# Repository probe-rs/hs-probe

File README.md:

# The Rusty High-speed Probe

This is an open hardware probe for the Serial Wire Debug (SWD) and JTAG protocol. It utilizes an
STM32F723 MCU which has an USB 2.0 High-speed Phy.

## Firmware

The firmware is available here and is open-source: https://github.com/probe-rs/hs-probe-firmware

## Features

There is an USB MUX on the board, so when the probe starts it enumerates in USB FS where one can
access the internal bootloader, and then when the firmware takes over it can switch to the USB HS.

* The output connector can either be:
    * The STDC14 connector used on STLink/V3 which is mounted by default.
    * Or the standard Cortex-M Debug (1.27mm, 10 pin) connector if one bends/removes the outer 2 pins on the connector.
* The programming connector is the Tag Connect TC2030, however for just loading firmware the USB bootloader is recommended.
* Resistive MUX between USB HS/FS.
* Castellated vias for all programming pins, power and 2 GPIOs.
* USB-C connector.
* Target 5V and `Vtarget` is protected with an ideal diode circuit to not have current flow from the target to the host.
* The probe support 1.8v - 3.3v signal voltage and `Vtarget`
* For compatibility (mainly with Tag-Connect TC2050), pin 7 on the STDC 14 can be connected to the protected 5V.

The schematic can be found in [the schematic PDF](schematic-v1.3.pdf).

## Cable Assembly

The hs-probe package sold on our [shop](https://shop.probe.rs) contains two 16 wire ribbon cables, three 14p connectors and one 10p connector.
You can make one cable with a 14p connector on each side and one cable with a 14p connector on one and a 10p connector on the other side. How to align the connectors is explained in the image below:

## License

This work is licensed under [CERN-OHL-P](cern_ohl_p_v2.txt).

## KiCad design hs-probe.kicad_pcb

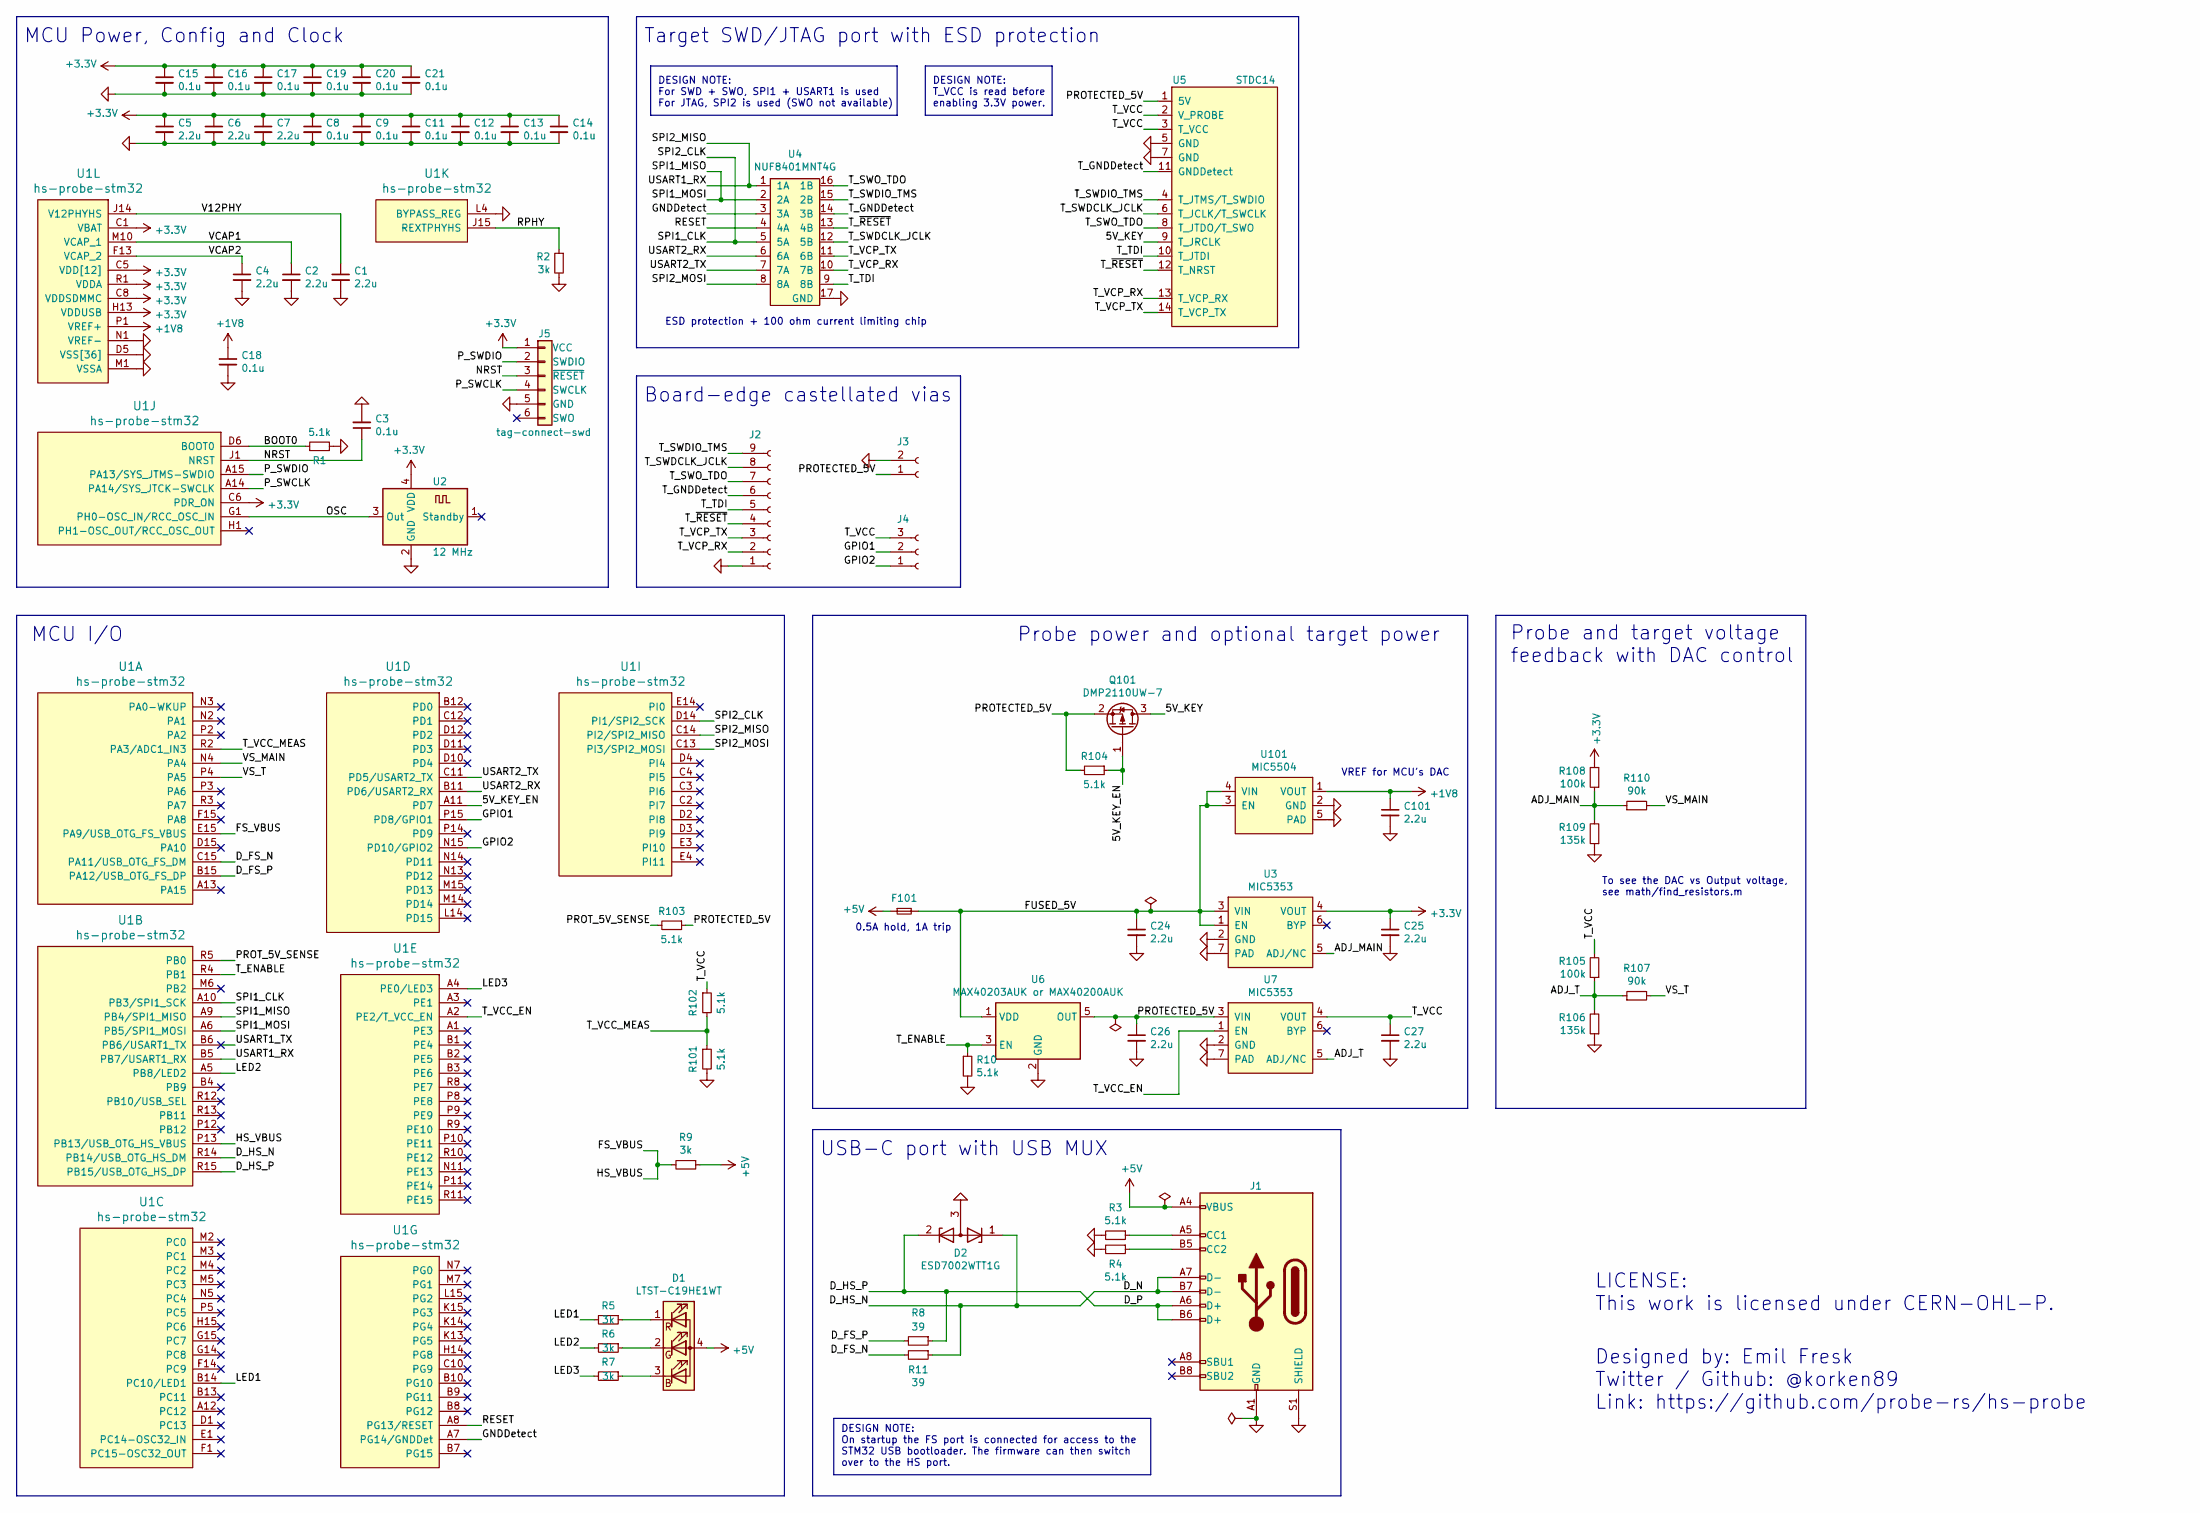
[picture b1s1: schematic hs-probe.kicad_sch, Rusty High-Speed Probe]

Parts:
C1, C2, C4, C5, C6, C7, C24, C25, C26, C27, C101: 2.2u; C_0402; Tolerance 10V, X5R
C3, C8, C9, C11, C12, C13, C14, C15, C16, C17, C18, C19, C20, C21: 0.1u; C_0402; Tolerance 25V, X7R
D1: LTST-C19HE1WT; LED_LiteOn_LTST-C19HE1WT; MPN LTST-C19HE1WT
D2: ESD7002WTT1G; SOT-323
F101: Fuse_Small; Fuse_0603_1608Metric
J1: USB_C_Receptacle_USB2.0; USB_C_Receptacle_USB4105; MPN C167321 (lcsc.com)
J2: Castellated Vias; 1x9_1.5mm_castellated
J3: Castellated Vias; 1x2_1.5mm_castellated
J4: Castellated Vias; 1x3_1.5mm_castellated
J5: tag-connect-swd; Tag-Connect_TC2030-IDC-NL_2x03_P1.27mm_Vertical
Q101: DMP2110UW-7; SOT-323
R1, R3, R4, R10, R101, R102, R103, R104: 5.1k; R_0402; Tolerance 1%
R2, R5, R6, R7, R9: 3k; R_0402; Tolerance 1%
R8, R11: 39; R_0402; Tolerance 1%
R105, R108: 100k; R_0402; Tolerance 1%
R106, R109: 135k; R_0402; Tolerance 1%
R107, R110: 90k; R_0402; Tolerance 1%
U1: hs-probe-stm32; UFBGA-201_10x10mm_Layout15x15_P0.65mm; MPN STM32F723IEK6
U2: 12 MHz; Crystal_4Pin_2.0x1.6mm; MPN KC2016Z12.0000C15XXK
U3, U7: MIC5353; DFN-6-1EP_1.6x1.6mm_P0.5mm_EP0.5x1.26mm
U4: NUF8401MNT4G; DFN-16-1EP_1.6x4mm_P0.5mm; MPN NUF8401MNT4G
U5: STDC14; PinHeader_2x07_FTSH-107-01-L-DV-K; MPN FTSH-107-01-L-DV-K
U6: MAX40203AUK or MAX40200AUK; SOT-23-5
U101: MIC5504; UDFN-4_1x1mm_P0.65mm

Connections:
+1V8: C18.1, C101.1, U1.P1 (VREF+), U101.1 (VOUT)
+3V3: C5.1, C6.1, C7.1, C8.1, C9.1, C11.1, C12.1, C13.1, C14.1, C15.1, C16.1, C17.1, C19.1, C20.1, C21.1, C25.1, J5.1 (VCC), R108.2, U1.C1 (VBAT), U1.C5 (VDD[12]), U1.C6 (PDR_ON), U1.C7 (VDD[12]), U1.C8 (VDDSDMMC), U1.C9 (VDD[12]), U1.F3 (VDD[12]), U1.G3 (VDD[12]), U1.G13 (VDD[12]), U1.H13 (VDDUSB), U1.J12 (VDD[12]), U1.J13 (VDD[12]), U1.K4 (VDD[12]), U1.N8 (VDD[12]), U1.N9 (VDD[12]), U1.N10 (VDD[12]), U1.R1 (VDDA), U2.4 (VDD), U3.4 (VOUT)
+5V: D1.4 (A), F101.1, J1.A4 (VBUS), J1.A9 (VBUS), J1.B4 (VBUS), J1.B9 (VBUS), R9.1
/5V_KEY: Q101.3 (D), U5.9 (T_JRCLK)
/5V_KEY_EN: Q101.1 (G), R104.1, U1.A11 (PD7)
/ADJ_MAIN: R108.1, R109.2, R110.1, U3.5 (ADJ/NC)
/ADJ_T: R105.1, R106.2, R107.1, U7.5 (ADJ/NC)
/BOOT0: R1.1, U1.D6 (BOOT0)
/D_FS_N: R11.2, U1.C15 (PA11/USB_OTG_FS_DM)
/D_FS_P: R8.2, U1.B15 (PA12/USB_OTG_FS_DP)
/D_HS_N: D2.1 (K), J1.A7 (D-), J1.B7 (D-), R11.1, U1.R14 (PB14/USB_OTG_HS_DM)
/D_HS_P: D2.2 (K), J1.A6 (D+), J1.B6 (D+), R8.1, U1.R15 (PB15/USB_OTG_HS_DP)
/FS_VBUS: R9.2, U1.E15 (PA9/USB_OTG_FS_VBUS), U1.P13 (PB13/USB_OTG_HS_VBUS)
/FUSED_5V: C24.1, F101.2, U3.1 (EN), U3.3 (VIN), U6.1 (VDD), U101.3 (EN), U101.4 (VIN)
/GNDDetect: U1.A7 (PG14/GNDDet), U4.3 (3A)
/GPIO1: J4.2, U1.P15 (PD8/GPIO1)
/GPIO2: J4.1, U1.N15 (PD10/GPIO2)
/LED1: R5.2, U1.B14 (PC10/LED1)
/LED2: R6.2, U1.A5 (PB8/LED2)
/LED3: R7.2, U1.A4 (PE0/LED3)
/NRST: C3.1, J5.3 (~RESET), U1.J1 (NRST)
/OSC: U1.G1 (PH0-OSC_IN/RCC_OSC_IN), U2.3 (Out)
/PROTECTED_5V: C26.1, J3.1, Q101.2 (S), R103.1, R104.2, U5.1 (5V), U6.5 (OUT), U7.3 (VIN)
/PROT_5V_SENSE: R103.2, U1.R5 (PB0)
/P_SWCLK: J5.4 (SWCLK), U1.A14 (PA14/SYS_JTCK-SWCLK)
/P_SWDIO: J5.2 (SWDIO), U1.A15 (PA13/SYS_JTMS-SWDIO)
/RESET: U1.A8 (PG13/RESET), U4.4 (4A)
/RPHY: R2.1, U1.J15 (REXTPHYHS)
/SPI1_CLK: U1.A10 (PB3/SPI1_SCK), U1.D14 (PI1/SPI2_SCK), U4.5 (5A)
/SPI1_MISO: U1.A6 (PB5/SPI1_MOSI), U1.A9 (PB4/SPI1_MISO), U4.2 (2A)
/SPI2_MISO: U1.B5 (PB7/USART1_RX), U1.C14 (PI2/SPI2_MISO), U4.1 (1A)
/SPI2_MOSI: U1.C13 (PI3/SPI2_MOSI), U4.8 (8A)
/T_ENABLE: R10.1, U1.R4 (PB1), U6.3 (EN)
/T_GNDDetect: J2.6, U4.14 (3B), U5.11 (GNDDetect)
/T_SWDCLK_JCLK: J2.8, U4.12 (5B), U5.6 (T_JCLK/T_SWCLK)
/T_SWDIO_TMS: J2.9, U4.15 (2B), U5.4 (T_JTMS/T_SWDIO)
/T_SWO_TDO: J2.7, U4.16 (1B), U5.8 (T_JTDO/T_SWO)
/T_TDI: J2.5, U4.9 (8B), U5.10 (T_JTDI)
/T_VCC: C27.1, J4.3, R102.1, R105.2, U5.2 (V_PROBE), U5.3 (T_VCC), U7.4 (VOUT)
/T_VCC_EN: U1.A2 (PE2/T_VCC_EN), U7.1 (EN)
/T_VCC_MEAS: R101.1, R102.2, U1.R2 (PA3/ADC1_IN3)
/T_VCP_RX: J2.2, U4.10 (7B), U5.13 (T_VCP_RX)
/T_VCP_TX: J2.3, U4.11 (6B), U5.14 (T_VCP_TX)
/T_~RESET: J2.4, U4.13 (4B), U5.12 (T_NRST)
/USART1_TX: U1.B6 (PB6/USART1_TX)
/USART2_RX: U1.B11 (PD6/USART2_RX), U4.6 (6A)
/USART2_TX: U1.C11 (PD5/USART2_TX), U4.7 (7A)
/V12PHY: C1.1, U1.J14 (V12PHYHS)
/VCAP1: C2.1, U1.M10 (VCAP_1)
/VCAP2: C4.1, U1.F13 (VCAP_2)
/VS_MAIN: R110.2, U1.N4 (PA4)
/VS_T: R107.2, U1.P4 (PA5)
GND: C1.2, C2.2, C3.2, C4.2, C5.2, C6.2, C7.2, C8.2, C9.2, C11.2, C12.2, C13.2, C14.2, C15.2, C16.2, C17.2, C18.2, C19.2, C20.2, C21.2, C24.2, C25.2, C26.2, C27.2, C101.2, D2.3 (A), J1.A1 (GND), J1.A12 (GND), J1.B1 (GND), J1.B12 (GND), J1.S1 (SHIELD), J2.1, J3.2, J5.5 (GND), R1.2, R2.2, R3.2, R4.2, R10.2, R101.2, R106.1, R109.1, U1.D5 (VSS[36]), U1.D7 (VSS[36]), U1.D8 (VSS[36]), U1.D9 (VSS[36]), U1.F2 (VSS[36]), U1.F6 (VSS[36]), U1.F7 (VSS[36]), U1.F8 (VSS[36]), U1.F9 (VSS[36]), U1.F10 (VSS[36]), U1.F12 (VSS[36]), U1.G2 (VSS[36]), U1.G6 (VSS[36]), U1.G7 (VSS[36]), U1.G8 (VSS[36]), U1.G9 (VSS[36]), U1.G10 (VSS[36]), U1.G12 (VSS[36]), U1.H6 (VSS[36]), U1.H7 (VSS[36]), U1.H8 (VSS[36]), U1.H9 (VSS[36]), U1.H10 (VSS[36]), U1.H12 (VSS[36]), U1.J6 (VSS[36]), U1.J7 (VSS[36]), U1.J8 (VSS[36]), U1.J9 (VSS[36]), U1.J10 (VSS[36]), U1.K6 (VSS[36]), U1.K7 (VSS[36]), U1.K8 (VSS[36]), U1.K9 (VSS[36]), U1.K10 (VSS[36]), U1.L4 (BYPASS_REG), U1.M1 (VSSA), U1.M8 (VSS[36]), U1.M9 (VSS[36]), U1.N1 (VREF-), U2.2 (GND), U3.2 (GND), U3.7 (PAD), U4.17 (GND), U5.5 (GND), U5.7 (GND), U6.2 (GND), U7.2 (GND), U7.7 (PAD), U101.2 (GND), U101.5 (PAD)
unnamed: D1.1 (RK), R5.1
unnamed: D1.2 (GK), R6.1
unnamed: D1.3 (BK), R7.1
unnamed: J1.A5 (CC1), R3.1
unnamed: J1.B5 (CC2), R4.1

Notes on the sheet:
Designed by: Emil Fresk Twitter / Github: @korken89 Link: https://github.com/probe-rs/hs-probe
Target SWD/JTAG port with ESD protection
Probe and target voltage feedback with DAC control
To see the DAC vs Output voltage, see math/find_resistors.m
USB-C port with USB MUX
DESIGN NOTE: T_VCC is read before enabling 3.3V power.
VREF for MCU's DAC
Board-edge castellated vias
MCU Power, Config and Clock
MCU I/O
ESD protection + 100 ohm current limiting chip
0.5A hold, 1A trip
Probe power and optional target power
DESIGN NOTE: On startup the FS port is connected for access to the STM32 USB bootloader. The firmware can then switch over to the HS port.
DESIGN NOTE: For SWD + SWO, SPI1 + USART1 is used For JTAG, SPI2 is used (SWO not available)
LICENSE: This work is licensed under CERN-OHL-P.

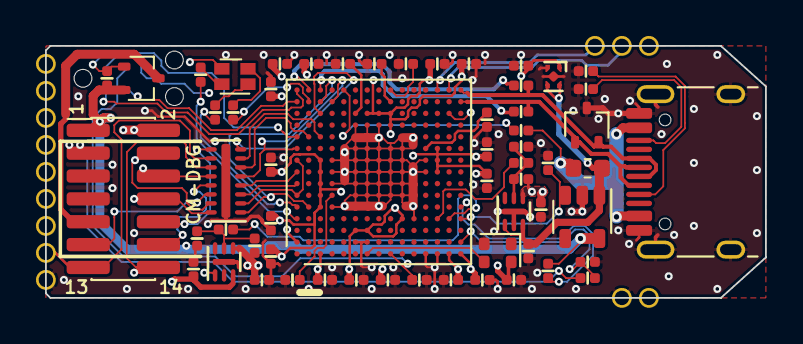
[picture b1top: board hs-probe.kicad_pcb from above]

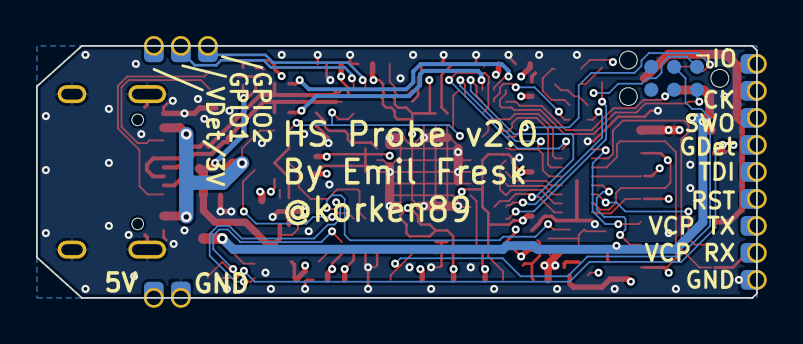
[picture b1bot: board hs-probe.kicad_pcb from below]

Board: 4 copper layers, 40.0 x 14.0 mm, 63 parts (4 on the bottom side), 57 nets.

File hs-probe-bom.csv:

Reference, Value, Footprint, Datasheet, MPN, Tolerance
"J1","USB_C_Receptacle_USB2.0","connectors:USB_C_Receptacle_USB4105","https://www.usb.org/sites/default/files/documents/usb_type-c.zip","C167321 (lcsc.com)",""
"R3","5.1k","passive:R_0402","~","","1%"
"R4","5.1k","passive:R_0402","~","","1%"
"FB1","Ferrite_Bead_Small","passive:R_0402","~","MMZ1005S601HT000","600 Ohm @ 100 MHz"
"U3","MIC5353","dfn:DFN-6-1EP_1.6x1.6mm_P0.5mm_EP0.5x1.26mm","https://ww1.microchip.com/downloads/en/DeviceDoc/mic5353.pdf","MIC5353-3.3YMT",""
"C25","2.2u","passive:C_0402","~","","10V, X5R"
"U7","MIC5353","dfn:DFN-6-1EP_1.6x1.6mm_P0.5mm_EP0.5x1.26mm","https://ww1.microchip.com/downloads/en/DeviceDoc/mic5353.pdf","MIC5353-3.3YMT",""
"C27","2.2u","passive:C_0402","~","","10V, X5R"
"C26","2.2u","passive:C_0402","~","","10V, X5R"
"C24","2.2u","passive:C_0402","~","","10V, X5R"
"C28","0.1u","passive:C_0402","~","","25V, X7R"
"R8","5.1k","passive:R_0402","~","","1%"
"U8","USB3740B-AI9","Package_DFN_QFN:UQFN-10_1.6x2.1mm_P0.5mm","http://ww1.microchip.com/downloads/en/DeviceDoc/00001725D.pdf","USB3740B-AI9-TR",""
"U1","hs-probe-stm32","bga:UFBGA-201_10x10mm_Layout15x15_P0.65mm","","STM32F723IEK6",""
"R9","1k","passive:R_0402","~","","1%"
"R102","5.1k","passive:R_0402","~","","1%"
"R101","5.1k","passive:R_0402","~","","1%"
"D1","LTST-C19HE1WT","LED_SMD:LED_LiteOn_LTST-C19HE1WT","https://optoelectronics.liteon.com/upload/download/DS22-2008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","LTST-C19HE1WT",""
"R7","1k","passive:R_0402","~","","5%"
"R6","1k","passive:R_0402","~","","5%"
"R5","1k","passive:R_0402","~","","5%"
"R1","5.1k","passive:R_0402","~","","1%"
"R2","3k","passive:R_0402","~","","1%"
"C3","0.1u","passive:C_0402","~","","25V, X7R"
"C1","2.2u","passive:C_0402","~","","10V, X5R"
"C2","2.2u","passive:C_0402","~","","10V, X5R"
"C4","2.2u","passive:C_0402","~","","10V, X5R"
"C5","2.2u","passive:C_0402","~","","10V, X5R"
"C6","2.2u","passive:C_0402","~","","10V, X5R"
"C7","2.2u","passive:C_0402","~","","10V, X5R"
"C23","0.1u","passive:C_0402","~","","25V, X7R"
"C22","0.1u","passive:C_0402","~","","25V, X7R"
"C21","0.1u","passive:C_0402","~","","25V, X7R"
"C20","0.1u","passive:C_0402","~","","25V, X7R"
"C19","0.1u","passive:C_0402","~","","25V, X7R"
"C18","0.1u","passive:C_0402","~","","25V, X7R"
"C17","0.1u","passive:C_0402","~","","25V, X7R"
"C16","0.1u","passive:C_0402","~","","25V, X7R"
"C15","0.1u","passive:C_0402","~","","25V, X7R"
"C14","0.1u","passive:C_0402","~","","25V, X7R"
"C13","0.1u","passive:C_0402","~","","25V, X7R"
"C12","0.1u","passive:C_0402","~","","25V, X7R"
"C11","0.1u","passive:C_0402","~","","25V, X7R"
"C10","0.1u","passive:C_0402","~","","25V, X7R"
"C9","0.1u","passive:C_0402","~","","25V, X7R"
"C8","0.1u","passive:C_0402","~","","25V, X7R"
"U2","12 MHz","crystals:Crystal_4Pin_2.0x1.6mm","https://global.kyocera.com/prdct/electro/product/pdf/clock_z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","KC2016Z12.0000C15XXK",""
"U4","NUF8401MNT4G","dfn:DFN-16-1EP_1.6x4mm_P0.5mm","http://www.onsemi.com/pub/Collateral/NUF8401MN-D.PDF","NUF8401MNT4G",""
"U5","STDC14","connectors:PinHeader_2x07_FTSH-107-01-L-DV-K","","FTSH-107-01-L-DV-K",""

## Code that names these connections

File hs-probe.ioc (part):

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Mcu.Name=STM32F723I(C-E)Kx
Mcu.Package=UFBGA176
Mcu.UserName=STM32F723IEKx
PA11.Mode=Device_Only
PA11.Signal=USB_OTG_FS_DM
PA12.Mode=Device_Only
PA12.Signal=USB_OTG_FS_DP
PA13.Mode=Serial_Wire
PA13.Signal=SYS_JTMS-SWDIO
PA14.Mode=Serial_Wire
PA14.Signal=SYS_JTCK-SWCLK
PA3.Signal=ADCx_IN3
PA4.Signal=COMP_DAC1_group
PA5.Signal=COMP_DAC2_group
PA9.Mode=Activate_VBUS
PA9.Signal=USB_OTG_FS_VBUS
PB10.GPIOParameters=GPIO_Label
PB10.GPIO_Label=USB_SEL
PB10.Signal=GPIO_Output
PB13.Mode=Activate_VBUS_FS
PB13.Signal=USB_OTG_HS_VBUS
PB14.Mode=Internal_Phy_Device
PB14.Signal=USB_OTG_HS_DM
PB15.Mode=Internal_Phy_Device
PB15.Signal=USB_OTG_HS_DP
PB3.Mode=Full_Duplex_Master
PB3.Signal=SPI1_SCK
PB4.Mode=Full_Duplex_Master
PB4.Signal=SPI1_MISO
PB5.Mode=Full_Duplex_Master
PB5.Signal=SPI1_MOSI
PB6.Mode=Asynchronous
PB6.Signal=USART1_TX
PB7.Mode=Asynchronous
PB7.Signal=USART1_RX
PB8.GPIOParameters=GPIO_Label
PB8.GPIO_Label=LED2
PB8.Signal=GPIO_Output
PC10.GPIOParameters=GPIO_Label
PC10.GPIO_Label=LED1
PC10.Signal=GPIO_Output
PD10.GPIOParameters=GPIO_Label
PD10.GPIO_Label=GPIO2
PD10.Signal=GPIO_Output
PD5.Mode=Asynchronous
PD5.Signal=USART2_TX
PD6.Mode=Asynchronous
PD6.Signal=USART2_RX
PD8.GPIOParameters=GPIO_Label
PD8.GPIO_Label=GPIO1
PD8.Signal=GPIO_Output
PE0.GPIOParameters=GPIO_Label
PE0.GPIO_Label=LED3
PE0.Signal=GPIO_Output
PE2.GPIOParameters=GPIO_Label
PE2.GPIO_Label=T_VCC_EN
PE2.Signal=GPIO_Output
PG13.GPIOParameters=GPIO_Label
PG13.GPIO_Label=RESET
PG13.Signal=GPIO_Output
PG14.GPIOParameters=GPIO_Label
PG14.GPIO_Label=GNDDet
PG14.Signal=GPIO_Output
PH0-OSC_IN.Mode=HSE-External-Clock-Source
PH0-OSC_IN.Signal=RCC_OSC_IN
PH1-OSC_OUT.Mode=HSE-External-Clock-Source
PH1-OSC_OUT.Signal=RCC_OSC_OUT
PI1.Mode=Full_Duplex_Master
PI1.Signal=SPI2_SCK
PI2.Mode=Full_Duplex_Master
PI2.Signal=SPI2_MISO
PI3.Mode=Full_Duplex_Master
PI3.Signal=SPI2_MOSI
RCC.HSE_VALUE=12000000
RCC.SYSCLKFreq_VALUE=216000000
RCC.SYSCLKSource=RCC_SYSCLKSOURCE_PLLCLK
board=custom

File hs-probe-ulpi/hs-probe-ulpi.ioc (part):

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PC3.Mode=External_Phy_Device
PA6.Mode=Full_Duplex_Master
PH0-OSC_IN.Signal=RCC_OSC_IN
Mcu.UserName=STM32F730R8Tx
PB10.Mode=External_Phy_Device
PC10.Signal=USART3_TX
PA11.Mode=Device_Only
PB11.Signal=USB_OTG_HS_ULPI_D4
PB15.Signal=SPI2_MOSI
PB13.Signal=USB_OTG_HS_ULPI_D6
RCC.SYSCLKSource=RCC_SYSCLKSOURCE_PLLCLK
PA12.Signal=USB_OTG_FS_DP
PB6.Signal=USART1_TX
PB6.Mode=Asynchronous
PC3.Signal=USB_OTG_HS_ULPI_NXT
PH0-OSC_IN.Mode=HSE-External-Clock-Source
RCC.HSE_VALUE=24000000
PB3.Mode=Full_Duplex_Master
PA14.Mode=Serial_Wire
PB14.Mode=Full_Duplex_Master
PB5.Mode=External_Phy_Device
PB7.Signal=USART1_RX
PA8.Signal=RCC_MCO_1
PH1-OSC_OUT.Mode=HSE-External-Clock-Source
Mcu.Package=LQFP64
PB1.Signal=USB_OTG_HS_ULPI_D2
PA6.Signal=SPI1_MISO
PB12.Mode=External_Phy_Device
PC11.Mode=Asynchronous
PB13.Mode=External_Phy_Device
PA3.Signal=USB_OTG_HS_ULPI_D0
PA5.Mode=External_Phy_Device
PA7.Mode=Full_Duplex_Master
PC11.Signal=USART3_RX
PC2.Signal=USB_OTG_HS_ULPI_DIR
PC10.Mode=Asynchronous
PC2.Mode=External_Phy_Device
PC0.Signal=USB_OTG_HS_ULPI_STP
PA0-WKUP.Signal=ADCx_IN0
PC0.Mode=External_Phy_Device
PA13.Signal=SYS_JTMS-SWDIO
PA3.Mode=External_Phy_Device
PA9.Mode=Full_Duplex_Master
PB11.Mode=External_Phy_Device
PA9.Signal=SPI2_SCK
PB10.Signal=USB_OTG_HS_ULPI_D3
PB14.Signal=SPI2_MISO
PA5.Signal=USB_OTG_HS_ULPI_CK
PB0.Mode=External_Phy_Device
board=custom
PB15.Mode=Full_Duplex_Master
PH1-OSC_OUT.Signal=RCC_OSC_OUT
PA13.Mode=Serial_Wire
Mcu.Name=STM32F730R8Tx
PB3.Signal=SPI1_SCK
RCC.SYSCLKFreq_VALUE=216000000
PB5.Signal=USB_OTG_HS_ULPI_D7
PA12.Mode=Device_Only
PB7.Mode=Asynchronous
PA11.Signal=USB_OTG_FS_DM
PA14.Signal=SYS_JTCK-SWCLK
PB1.Mode=External_Phy_Device
PA8.Mode=Clock-out-1
PB0.Signal=USB_OTG_HS_ULPI_D1
PB12.Signal=USB_OTG_HS_ULPI_D5
PA7.Signal=SPI1_MOSI

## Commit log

2020-03-31 README
2020-03-31 Added missing keep-out under MCU
2020-03-31 Fixes on STDC14 connector, fixed component courtyards
2020-03-31 Silkscreen cleanup
2020-03-31 Added JTAG on SPI2
2020-04-01 Minor updates
2020-04-01 Shorted SPI1 MISO/MOSI, rotated connector
2020-04-01 Added cache
2020-04-06 Added ESD protection, fixed silkscreen
2020-04-14 Updated LED for a more commonly available one
2020-05-21 Fix errors
2020-07-15 Added USB Mux to start with FS and then switch to HS
2020-07-16 Updated BOM
2020-07-16 Added Castellated Vias
2020-07-16 Added 2 GPIO to headers
2020-07-16 Improved images
2020-07-16 Smaller images
2020-07-16 Rotated castellated vias the right way
2020-07-16 Cleanup
2020-07-16 Updated images
2020-07-17 Minor PCB cleanup, more GND vias
2020-07-19 Updated design from review comment
2020-07-19 Major schematic cleanup
2020-07-19 Updated README, images and added schematic PDF
2020-07-19 Moved to tag connect
2020-07-19 Fixed ERC warnings
2020-07-19 Added license, dimensions and manufacturing specs
2020-07-19 Updated 3D models to FTSH-107-01-L-DV-K
2020-07-19 Improved ESD protection + current limiting clarity
2020-07-20 Thickened up power traces under MCU
2020-08-06 Now using a 2x1.6mm crystal
2020-09-04 Updated crystal footprint
2020-09-15 Updated README and minor HW cleanup
2020-10-04 Moved to 3k resistors for the LEDs and USB detect
2020-10-12 Save
2020-10-20 Added ideal diode to target power, fixed programming connector
2020-10-20 Added missing pull-down resistor on ideal diode
2020-10-20 Resistor name update
2020-11-04 inital commit
2020-11-04 Revert accidential commits that should have gone to a fork
2020-11-06 Small fixes
2020-11-18 Added 5V target sense line
2020-11-28 v1.3, now can connect 5V to pin 7 of STDC14
2020-11-28 Link fix
2020-11-28 Changed ferrite bead for fuse
2021-05-25 v1.4, now without the USB mux
2021-08-24 Add assembly instructions
2021-08-26 v1.4 schematic, README, and images
2022-01-07 v2.0 and kicad v6
